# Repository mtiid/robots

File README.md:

robots
======

There are currently two servers, one for the hiduino bots (JackBox, BreakBot, Clappers, GanaPati, MahaDevi), 
and one for the serial bots (Lydia, MarimBot, StringThing).

The two servers should always be left running. In the case that they aren't, simply type the following into terminal.

    $ robots

This will run a bash function that kills any running ChucK programs, and then starts the server.

    robots() {
        SERVICE='chuck'

        if ps ax | grep -v grep | grep $SERVICE > /dev/null
        then
            echo "$SERVICE killing running chuck programs"
            killall chuck
        fi

        chuck ~/git/robots/serial-robot-server/master.ck --port:8888 &
        chuck ~/git/robots/hiduino-robot-server/master.ck --port:8889
    }

communication
-------------

**IT IS NOT RECOMMENEDED TO CONNECT WIRELESSLY**

While it is entirely possible to connect using the wireless network, you will definitely experience lag and dropped OSC messages.

To connect using ChucK using OSC with a LAN connection:

    OscOut out;

    ("chuckServer.local", 50000) => out.dest;

To send to a robot using its OSC address.

    out.start("/clappers");
    out.add(note);
    out.add(velocity);
    out.send();

A full list of robots by their OSC addresses

    // hiduino robots
    /drumBot
    /clappers
    /ganapati
    /jackbass
    /jackgtr
    /jackperc
    /devibot

    // serial robots
    /marimba
    /trimpspin
    /trimpbeat
	/stringthing
    /snapperbot
    /rattletron

To connect using MIDI, see the [midi-robot-client](https://github.com/MTIID/robots/tree/master/midi-robot-client) repo.

quick-test-code
---------------
Copy/paste this to quickly see if you can successfully connect using a wired connection.

    OscOut out;
    ("chuckServer.local", 50000) => out.dest;

    while(true) {
        out.start("/clappers");
        out.add(Math.random2(0, 20));
        out.add(127);
        out.send();
        10::ms => now;
    }

maintenance and troubleshooting
------------

In general, if there the server is acting up a simple restart of the ChucK
code will clear things up 90% of the time. This can be done by
opening up terminal and entering in the "robots" command described above.
Also check for multiple instances of terminal that might be 
running on the robots computer. If needed, close the
extra instances and relaunch the server. 

If one of the bots is not responding, first check to see if the bot has
power connected. Some bots, such as Lydia and JackBox, can sometimes be 
accidentally unplugged. Likewise, check the USB cable going to the bot in
question, and if JackBox is the bot that is acting up also check the two 
MIDI cables. If the cable looks good on the bot end, 
don't forget to check the hub end as well. 

If more than one robot is unresponsive, there is a chance that something went 
wrong with one, or more, of the USB hubs. 
Check to see that the hubs are plugged into their power 
bricks, that they are turned on, and plugged into the robots computer.

If you are running code on your computer through the MIDI Client 
and are having issues this might help:

1. Test using ChucK or another programming language without the MIDI Client. 
    - Sometimes the MIDI Client can be a bit finicky, this will tell you if
        its the client itself or some other link in the chain.
2. Restart the MIDI Client (after closing the instance of it).
    - "Uninstall Everything" - Owen Vallis
3. Make sure you have the most recent version of the code ('git pull' the repo).
    - This repo is constantly being updated, the most recent code will be more 
        stable, there is a chance the issue you are running into has been fixed.
4. Test your code (or set) or the robots computer.
    - Is it your computer, or the server?
5. Are any of the bots working, or is it just one or two that is not responding?

programmers
-----------

hiduino-robot-server and midi-robot-client written by Ness Morris and Bruce Lott in the winter of 2013-2014, based on code by Ajay Kapur, Owen Vallis, and Dimitri Diakopoulos

serial-robot-server written by Eric Heep in the summer of 2014. Code is currently maintained by Nathan Shaw.

if there are any questions, concerns or issues feel free to email Nathan at: nathanshaw@alum.calarts.edu

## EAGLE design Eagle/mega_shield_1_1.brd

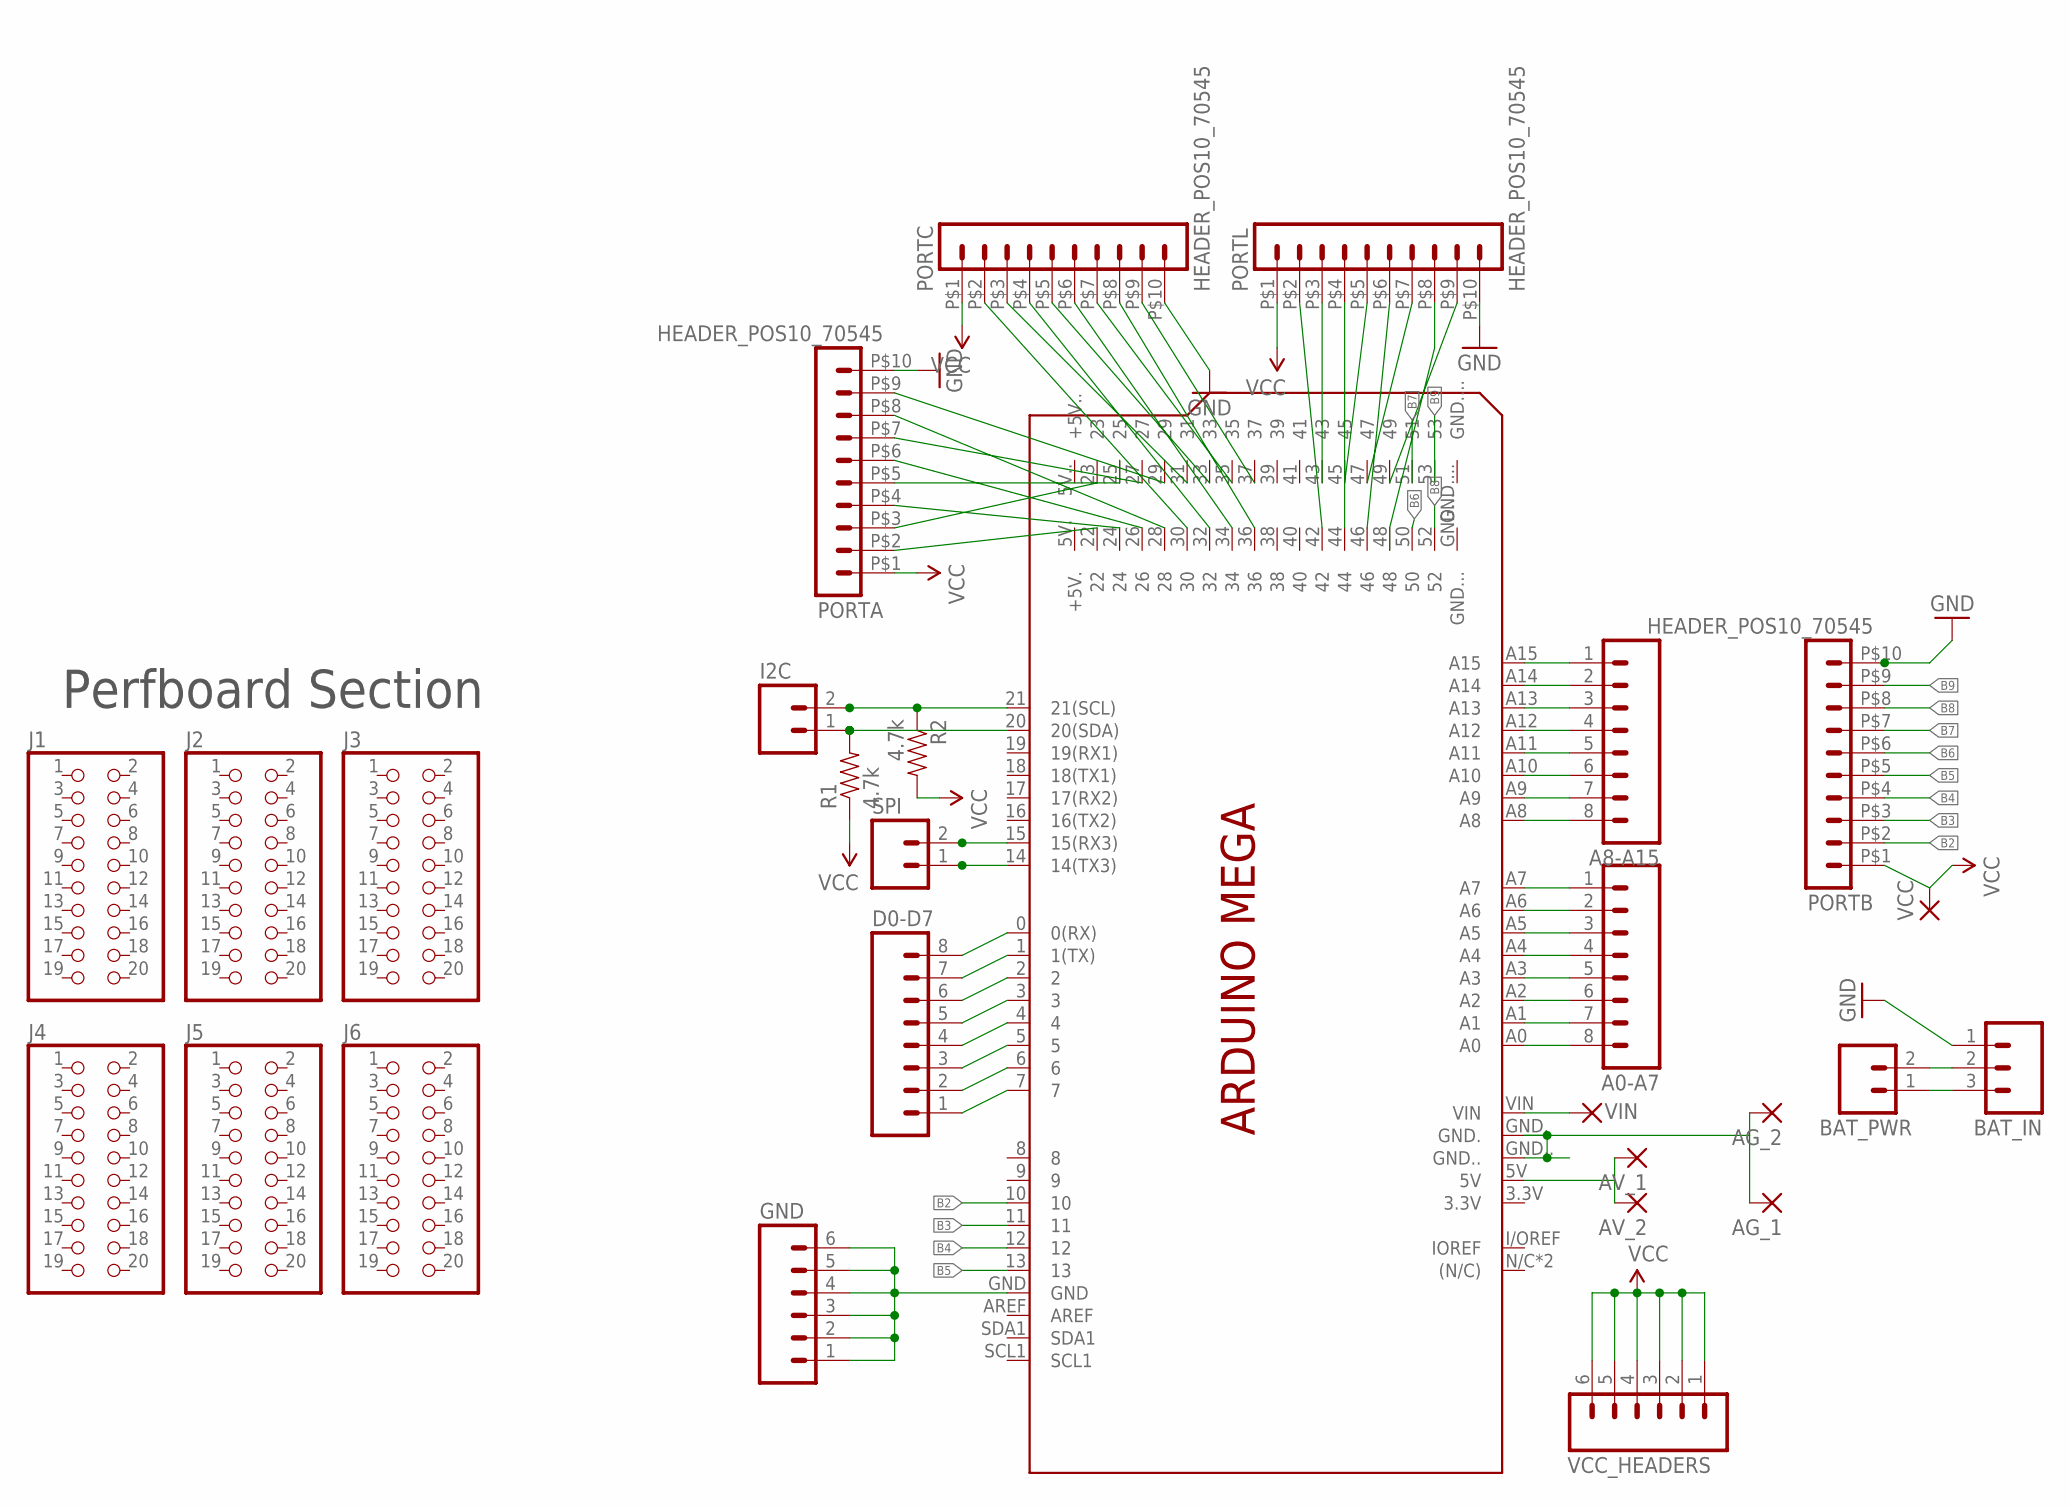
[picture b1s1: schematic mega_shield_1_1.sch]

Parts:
A0-A7, A8-A15: M08; 1X08_ROUND
AG_1, AG_2: 2,54/1,0
AV_1, AV_2: 2,54/1,0
BAT_IN: M03POLAR; MOLEX-1X3
BAT_PWR: M021X02_NO_SILK; 1X02_NO_SILK
D0-D7: M08; 1X08_ROUND
GND: M06SILK_FEMALE_PTH; 1X06
I2C: M02PTH; 1X02
J1, J2, J3, J4, J5, J6: PINHD-2X10; 2X10
PCB1: ARDUINO_MEGA
PORTA: HEADER_POS10_70545; 70545-POS10
PORTB: HEADER_POS10_70545; 70545-POS10
PORTC: HEADER_POS10_70545; 70545-POS10
PORTL: HEADER_POS10_70545; 70545-POS10
R1, R2: 4.7k; AXIAL-0.3
SPI: M02PTH; 1X02
VCC: 2,54/0,9
VCC_HEADERS: M06SILK_FEMALE_PTH; 1X06
VIN: 2,54/1,0

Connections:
B2: PCB1.10, PORTB.P$2 (2)
B3: PCB1.11, PORTB.P$3 (3)
B4: PCB1.12, PORTB.P$4 (4)
B5: PCB1.13, PORTB.P$5 (5)
B6: PCB1.50, PORTB.P$6 (6)
B7: PCB1.51, PORTB.P$7 (7)
B8: PCB1.52, PORTB.P$8 (8)
B9: PCB1.53, PORTB.P$9 (9)
GND: BAT_IN.1, PORTA.P$10 (10), PORTB.P$10 (10), PORTC.P$10 (10), PORTL.P$10 (10)
GND_PI: AG_1.1, AG_2.1, PCB1.GND., PCB1.GND..
unnamed: PCB1.22, PORTA.P$2 (2)
unnamed: PCB1.23, PORTA.P$3 (3)
unnamed: PCB1.24, PORTA.P$4 (4)
unnamed: PCB1.25, PORTA.P$5 (5)
unnamed: PCB1.26, PORTA.P$6 (6)
unnamed: PCB1.27, PORTA.P$7 (7)
unnamed: PCB1.28, PORTA.P$8 (8)
unnamed: PCB1.29, PORTA.P$9 (9)
unnamed: PCB1.14 (14(TX3)), SPI.1
unnamed: PCB1.15 (15(RX3)), SPI.2
unnamed: PCB1.30, PORTC.P$2 (2)
unnamed: PCB1.31, PORTC.P$3 (3)
unnamed: PCB1.32, PORTC.P$4 (4)
unnamed: PCB1.33, PORTC.P$5 (5)
unnamed: PCB1.34, PORTC.P$6 (6)
unnamed: PCB1.35, PORTC.P$7 (7)
unnamed: PCB1.36, PORTC.P$8 (8)
unnamed: PCB1.37, PORTC.P$9 (9)
unnamed: PCB1.42, PORTL.P$2 (2)
unnamed: PCB1.43, PORTL.P$3 (3)
unnamed: PCB1.44, PORTL.P$4 (4)
unnamed: PCB1.45, PORTL.P$5 (5)
unnamed: PCB1.46, PORTL.P$6 (6)
unnamed: PCB1.47, PORTL.P$7 (7)
unnamed: PCB1.49, PORTL.P$9 (9)
unnamed: BAT_IN.2, BAT_PWR.2
unnamed: A0-A7.1, PCB1.A7
unnamed: A0-A7.2, PCB1.A6
unnamed: PCB1.48, PORTL.P$8 (8)
unnamed: A0-A7.3, PCB1.A5
unnamed: A0-A7.4, PCB1.A4
unnamed: A0-A7.5, PCB1.A3
unnamed: A0-A7.6, PCB1.A2
unnamed: A0-A7.7, PCB1.A1
unnamed: I2C.1, PCB1.20 (20(SDA)), R1.P$2 (2)
unnamed: I2C.2, PCB1.21 (21(SCL)), R2.P$1 (1)
unnamed: A0-A7.8, PCB1.A0
unnamed: A8-A15.8, PCB1.A8
unnamed: A8-A15.7, PCB1.A9
unnamed: A8-A15.6, PCB1.A10
unnamed: A8-A15.5, PCB1.A11
unnamed: A8-A15.4, PCB1.A12
unnamed: A8-A15.3, PCB1.A13
unnamed: A8-A15.2, PCB1.A14
unnamed: A8-A15.1, PCB1.A15
unnamed: D0-D7.1, PCB1.7
unnamed: D0-D7.2, PCB1.6
unnamed: D0-D7.3, PCB1.5
unnamed: D0-D7.4, PCB1.4
unnamed: D0-D7.5, PCB1.3
unnamed: D0-D7.6, PCB1.2
unnamed: D0-D7.7, PCB1.1 (1(TX))
unnamed: D0-D7.8, PCB1.0 (0(RX))
unnamed: GND.1, GND.2, GND.3, GND.4, GND.5, GND.6, PCB1.GND
unnamed: AV_1.1, AV_2.1, PCB1.5V
unnamed: BAT_IN.3, BAT_PWR.1
VCC: PORTA.P$1 (1), PORTB.P$1 (1), PORTC.P$1 (1), PORTL.P$1 (1), R1.P$1 (1), R2.P$2 (2), VCC.1, VCC_HEADERS.1, VCC_HEADERS.2, VCC_HEADERS.3, VCC_HEADERS.4, VCC_HEADERS.5, VCC_HEADERS.6
VIN: PCB1.VIN, VIN.1

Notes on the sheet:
Perfboard Section

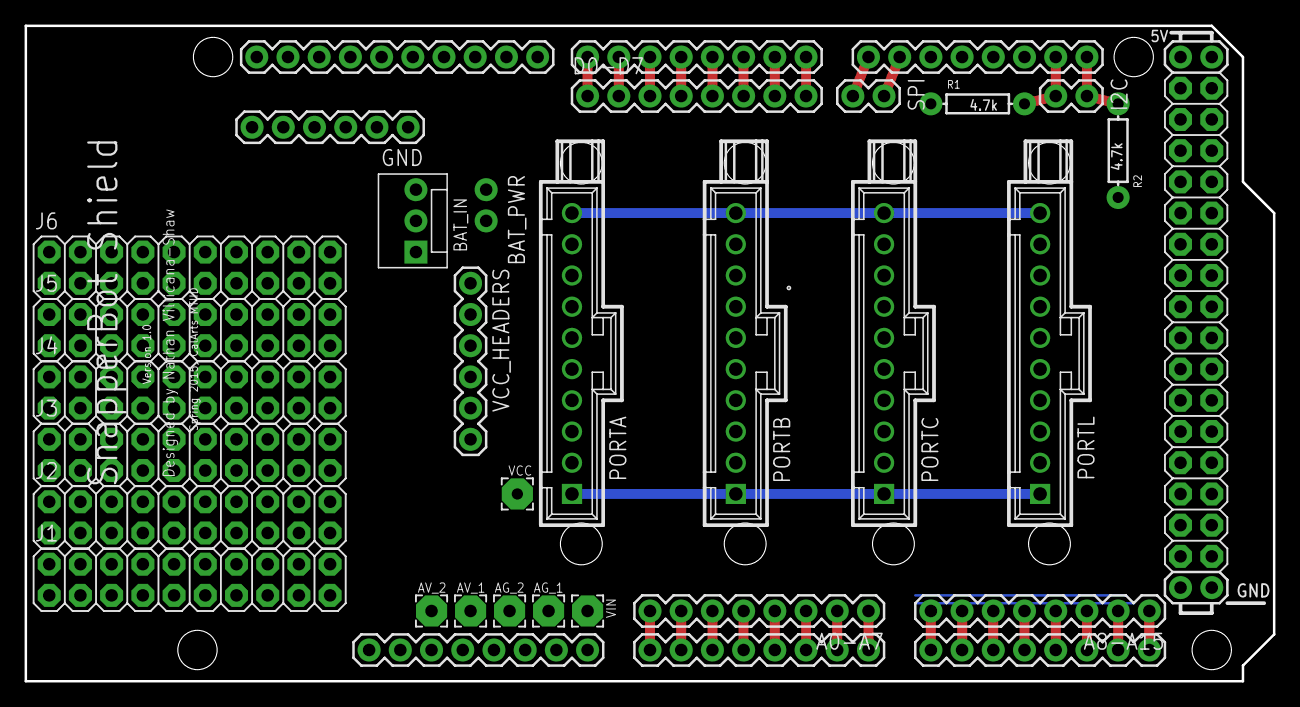
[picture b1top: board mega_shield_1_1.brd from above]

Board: 2 copper layers, 101.6 x 53.3 mm, 28 parts (0 on the bottom side), 68 nets.

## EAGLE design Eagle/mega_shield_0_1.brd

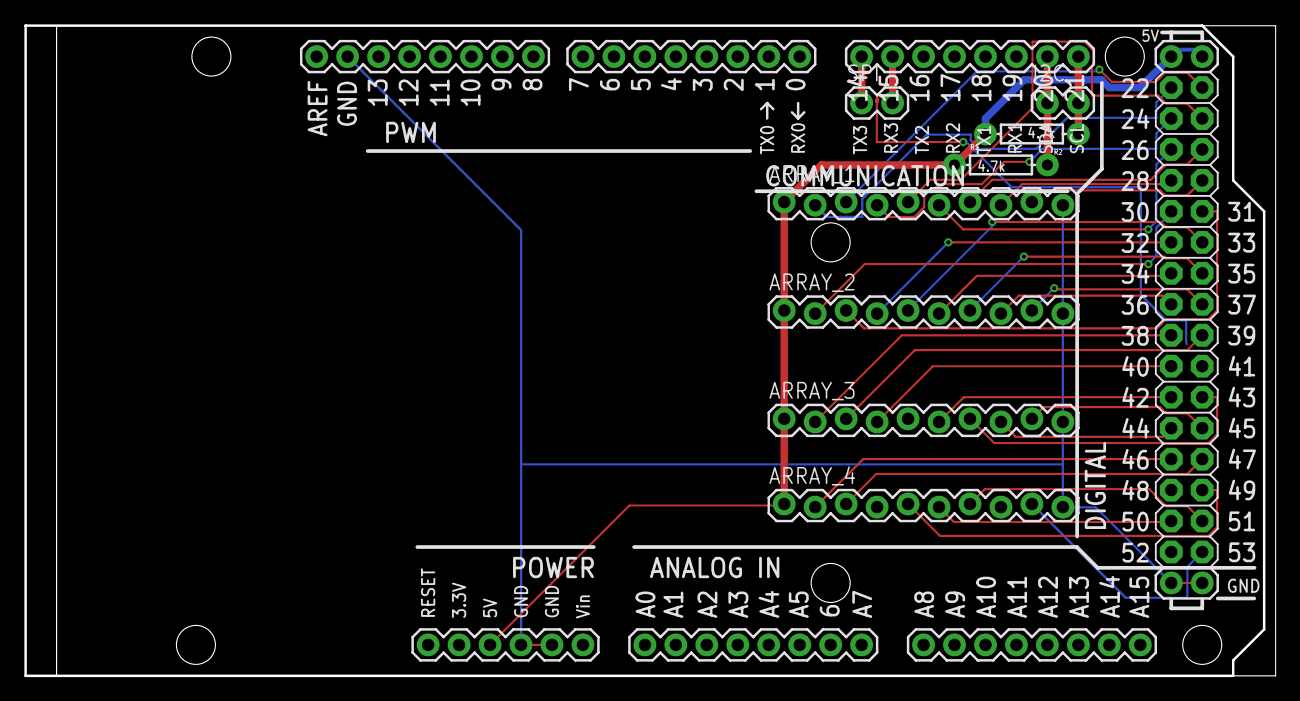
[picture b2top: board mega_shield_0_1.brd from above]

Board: 2 copper layers, 102.4 x 53.3 mm, 9 parts (0 on the bottom side), 35 nets.

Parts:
ARRAY_1, ARRAY_2, ARRAY_3, ARRAY_4: M10LOCK; 1X10_LOCK
I2C: 1X02
PCB1: ARDUINO-MEGAFULL; ARDUINO_MEGA
R1, R2: 4.7k; AXIAL-0.3
SPI: 1X02

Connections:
GND: ARRAY_1.10, ARRAY_2.10, ARRAY_3.10, ARRAY_4.10, PCB1.GND@0, PCB1.GND@1, PCB1.GND@2, PCB1.GND@3, PCB1.GND@4
unnamed: ARRAY_1.2, PCB1.22
unnamed: ARRAY_1.9, PCB1.29
unnamed: ARRAY_1.3, PCB1.23
unnamed: ARRAY_1.4, PCB1.24
unnamed: ARRAY_1.5, PCB1.25
unnamed: ARRAY_1.6, PCB1.26
unnamed: ARRAY_1.7, PCB1.27
unnamed: ARRAY_1.8, PCB1.28
unnamed: PCB1.14, SPI.1
unnamed: PCB1.15, SPI.2
unnamed: ARRAY_2.2, PCB1.30
unnamed: ARRAY_2.3, PCB1.31
unnamed: ARRAY_2.4, PCB1.32
unnamed: ARRAY_2.5, PCB1.33
unnamed: ARRAY_2.6, PCB1.34
unnamed: ARRAY_2.7, PCB1.35
unnamed: ARRAY_2.8, PCB1.36
unnamed: ARRAY_2.9, PCB1.37
unnamed: ARRAY_3.2, PCB1.38
unnamed: ARRAY_3.3, PCB1.39
unnamed: ARRAY_3.4, PCB1.40
unnamed: ARRAY_3.6, PCB1.42
unnamed: ARRAY_3.7, PCB1.43
unnamed: ARRAY_3.8, PCB1.44
unnamed: ARRAY_3.9, PCB1.45
unnamed: ARRAY_4.2, PCB1.46
unnamed: ARRAY_4.3, PCB1.47
unnamed: ARRAY_4.5, PCB1.49
unnamed: ARRAY_4.6, PCB1.50
unnamed: ARRAY_4.7, PCB1.51
unnamed: ARRAY_4.9, PCB1.53
unnamed: I2C.1, PCB1.20, R1.P$2
unnamed: I2C.2, PCB1.21, R2.P$1
VCC: ARRAY_1.1, ARRAY_2.1, ARRAY_3.1, ARRAY_4.1, PCB1.5V@0, PCB1.5V@1, PCB1.5V@2, R1.P$1, R2.P$2

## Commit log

2015-01-30 reorganization
2015-01-30 small typo
2015-01-30 erased stuff
2015-01-30 typos abound
2015-01-30 removed $ signs
2015-01-30 updated terminal commands
2015-01-30 typo
2015-01-30 added time for no crash
2015-01-30 typo stuff
2015-01-30 typo in name, of all places
2015-01-30 fixed broken link
2015-02-20 Added Firmware
    basic functions for sweeping, individual flip and dynamics
2015-02-20 Cleaned Things Up
2015-02-21 Fixed a few minor bugs
2015-02-21 shortened test sequence
2015-03-06 It Works! Sort Of
2015-03-08 Version 1.0
    Party Party Party
2015-03-08 adaptive arduino finding, perhaps
2015-03-08 updated ports
2015-03-08 added version optimized for pi
2015-03-08 pi opt 2
2015-03-08 switho
2015-03-08 bug cleaning
2015-03-09 Optimized Pi Code
2015-03-09 little changes
2015-03-09 errors
2015-03-09 safe created 0
2015-03-09 Working Stable Version on the Pi (version 1_0)
2015-03-09 <<<< VERSION 1.0 >>>>
2015-03-13 robot composition added
    also optimized code
2015-03-13 worked more on optimization
2015-03-13 Fixed lots o bugs, got chuck test file
2015-03-18 Optimization Work
    Added Eagle Files
2015-03-20 Optimizing Chuck
    Adding bitpicking for the chuck code, still whip
2015-03-20 added support for rhythms
2015-03-24 added startup test code for firmware
2015-03-26 Added code for Startup tests
2015-03-30 fixed marimba scale, added last note
2015-03-30 adjusted scale, it was off by one
2015-03-30 bye bye swap file
2015-03-31 Started rewriting serial
2015-04-06 Finalized firmware for master and slaves
2015-04-09 Pounded at serial for a bit
2015-04-10 bugs??
2015-04-10 PYTHON
    scraped uneeded code
    added OSC support
    changed everything over to python
    got rid of version histories
    many other changes
2015-04-12 added osc tester for python
2015-04-12 shhs
2015-04-13 updated readme to discourage using wireless communication
2015-04-13 formatting
2015-04-13 more formatting
2015-04-20 changed actuator order, fill in missing note
2015-04-20 renamed wireless.ck to hub.ck, not encouraging wireless transmission anymore
2015-04-20 added bash function to start server faster
2015-04-27 added 5-minute-phase to the server
2015-04-29 changed name in file
2015-04-29 added clock phase, current set to phase on the hour indefinitely
2015-04-30 highest note is the pulse
2015-04-30 added a version of clock-phase for the raspberry pi
2015-09-17 updated serial protocol to require a parity byte, upped baud rate, should stop most of the crashes we had last semester
2015-09-17 removed debug
2015-09-17 small update
2015-10-22 small formatting thing
2015-10-22 corrected /drumBot OSC address, updated over-actuate
2015-10-28 fixed that syntax error
2015-10-28 fixed another syntax error
2015-10-28 fixed midi osc addresses
2015-10-28 updated osc port
2015-10-28 added new function for marimba
2015-11-02 update to fix trimpbeat and trimpspin
2015-11-04 cleanup
2015-11-04 gitignore
2015-11-05 midi thru
2015-11-05 closed min at the end of client runner to (hopefully) avoid segfaults
2015-11-05 removed unnecessary midi thru versions
2015-11-05 revert min close sillyness
2015-11-05 new thing for things
2016-01-20 added proposal for NIME and a NIME folder that will house other things
2016-01-20 Added Digital Rain Nime Prop
2016-01-21 a few minor changes, replaced the dummy catagories with what they actually are
2016-01-21 a few minor changes
2016-01-21 More Proposal Additions
2016-01-21 Added Photos
2016-01-21 added all the most rescent media files
2016-01-21 added .ds_stores to gitignore
2016-01-22 a few minor changes to the proposal
2016-01-22 added selfie and a few links to the docx
2016-01-22 found better picture
2016-01-22 removed local .DS_Store files
2016-01-22 added my bio pic and started on the artist bio for myself
2016-01-22 a few minor changes to my artist bio
2016-01-22 mutalation
2016-01-22 a few more minor changes
2016-01-30 updated the pages proposal and added a new one
2016-03-07 started on more advanced version of the board
2016-03-10 pi stuff
2016-05-24 moved test python files to a tests folder
2016-05-24 fixed minor typo
2016-06-22 added the groove program to the repo
2016-06-22 added DS_Store files to the gitignore
2016-07-21 updated to reflect parity byte change in the robot code
2016-09-23 added test scripts for testing the different robots
2016-09-23 added serial version of snapperbot firmware
2016-09-26 created alternate version of snapperbot firmware that can accept note and velocity messages
2016-09-29 comming to move to feature branch
2016-09-29 asdf
2016-09-30 added in ableton set for JackBox
2016-09-30 updated the Jackbox test and the robot test
2016-09-30 added ableton set for jackbox remote use
2016-09-30 updated remote jackbox set
2016-09-30 fixed type of clapper test
2016-10-02 fixing bug in marimbot code pt. 1
2016-10-02 rearanged note order for Marimbot, only missing one note now...
2016-10-06 added ableton set for the marimbot
2016-10-13 restructured test programs
2016-10-14 added lydia test to repo
2016-10-16 added stringThing and snapperbots to server code
2016-10-16 added tests for lydia, added rough of the master ableton set
2016-10-20 updated lydia test
2016-10-21 updated tests for some bots
2016-10-23 adding the snapperbots to the server
2016-10-23 updated server stuff
2016-11-21 updated midi client a little bit
2016-12-02 fixed type for ganapati
2017-01-15 updated main readme, removed some legacy code
2017-02-05 added demo script to repo
2017-02-10 made it so all bots can be addressed using the midi-client with midi note 60 as the start of their scale
2017-02-13 updated the chuck test script for BreakBot
2017-02-13 added MahaDevi folder for the test code folder
2017-02-14 updated most of the test examples for chuck
2017-02-23 cleaned up the lydia chuck code tests
2017-02-28 added tammy to the server
2017-03-29 added blowbot to the server
2017-04-01 added blowbot test file and fixed typo in blowbot.ck
2017-04-20 removed some swap files, removed git diff noise from .gitignore
2017-04-20 removed some swap files, removed git diff noise from .gitignore pt. 2
2017-05-04 fix midi client + add windbot
2017-05-04 windbot stuff
2017-06-15 some tests for windbot

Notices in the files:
parts and their libraries:
SparkFun-Boards: Licensing: Creative Commons ShareAlike 4.0 International - https://creativecommons.org/licenses/by-sa/4.0
